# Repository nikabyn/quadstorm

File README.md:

# Project quadstorm (C010 Principles of Mobile Robotics)

## Architecture

## Mainboard

## Parts-List:
- [BT2.0 550mAh 1S Battery](https://betafpv.com/products/bt2-0-550mah-1s-battery-4pcs#:~:text=Weight:%2013.99g/pc,VS%20450mAh%20Battery)
- IMU [BMI323](https://www.bosch-sensortec.com/products/motion-sensors/imus/bmi323/)
- Motors: [4x 2S Bldc 1503](https://www.amazon.de/dp/B0CK2KT3R3)
- ESP32-C6 ([ESP32-C6 Supermini](https://wiki.raudys.com/doku.php?id=esp32:esp32-c6_super_mini_board) / [DFR1117](https://wiki.dfrobot.com/SKU_DFR1117_Beetle_ESP32_C6))
- 74LS04 (Hex-Inverter), 74LS138 3-to-8 demux)
- [FVT LittleBee ESC 20A 2-4S](https://de.aliexpress.com/item/1005010298051292.html)
- Generic DJI compatible props
- 3d Printed Frame
- Custom Mainboard (manufactured via CNC Router)
- 12 M2x8 Screws

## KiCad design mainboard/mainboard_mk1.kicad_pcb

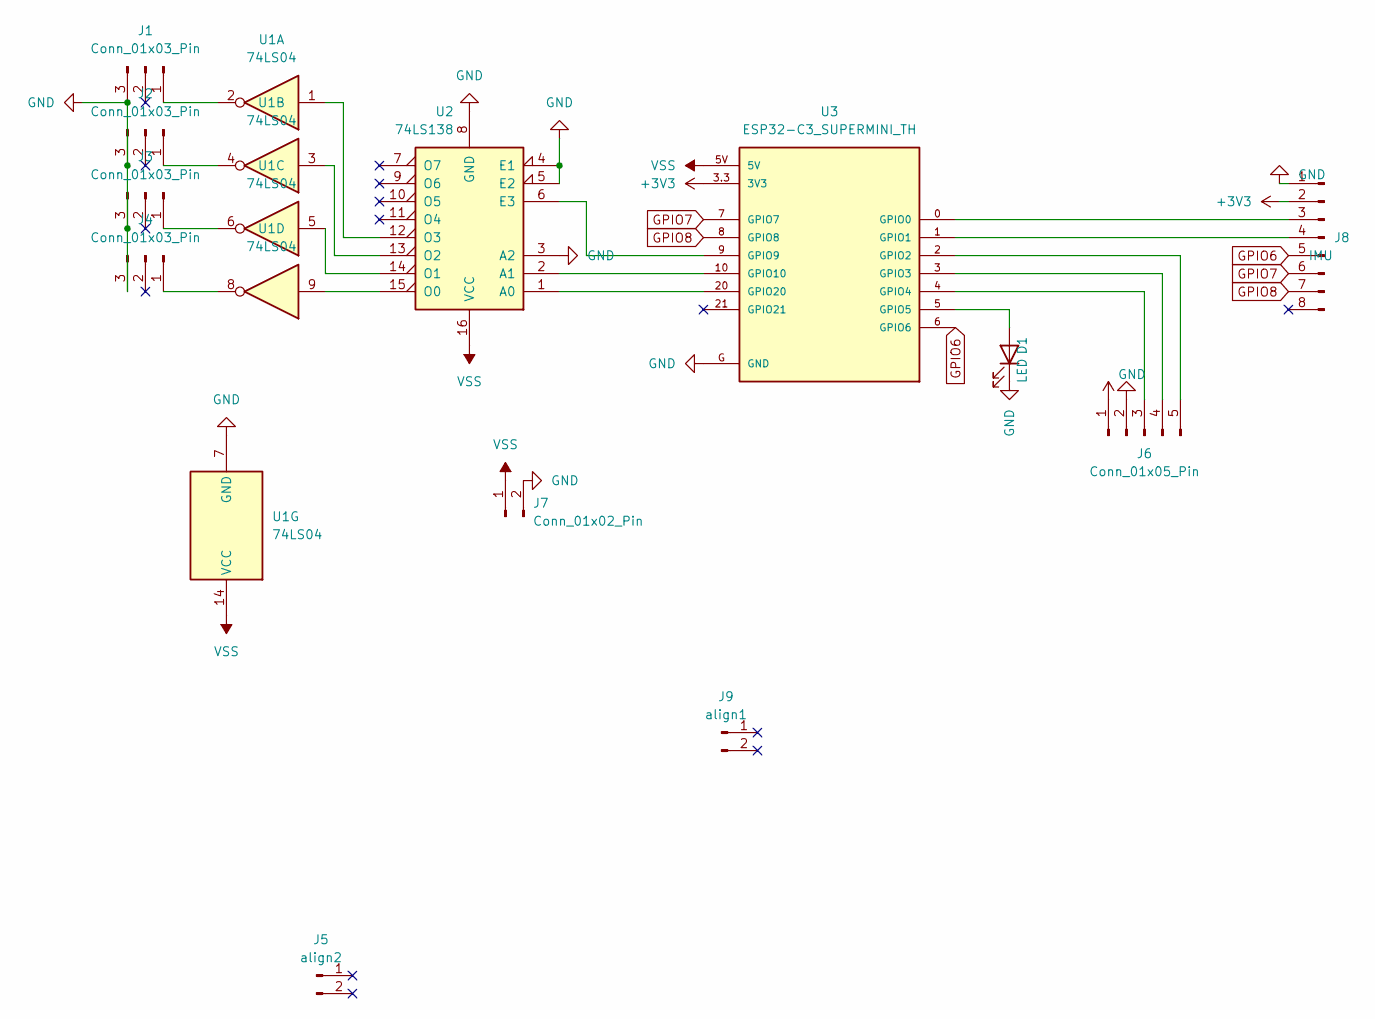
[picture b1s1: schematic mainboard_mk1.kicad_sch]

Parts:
D1: LED; LED_D3.0mm
J1, J2, J3, J4: Conn_01x03_Pin; PinHeader_1x03_P2.54mm_Vertical
J5: align2; PinHeader_1x02_P2.54mm_Vertical
J6: Conn_01x05_Pin; PinHeader_1x06_P2.54mm_Horizontal
J7: Conn_01x02_Pin; PinHeader_1x02_P2.54mm_Vertical
J8: IMU; PinHeader_1x08_P2.54mm_Vertical
J9: align1; PinHeader_1x02_P2.54mm_Vertical
U1: 74LS04; DIP-14_W7.62mm
U2: 74LS138; DIP-16_W7.62mm
U3: ESP32-C3_SUPERMINI_TH; MODULE_ESP32-C3_SUPERMINI_TH

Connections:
+3V3: J6.1, J8.2, U3.3.3 (3V3)
GND: D1.1 (K), J1.3, J2.3, J3.3, J4.3, J6.2, J7.2, J8.1, U1.7 (GND), U2.3 (A2), U2.4 (E1), U2.5 (E2), U2.8 (GND), U3.G (GND)
GPIO6: J8.5, U3.6 (GPIO6)
GPIO7: J8.6, U3.7 (GPIO7)
GPIO8: J8.7, U3.8 (GPIO8)
unnamed: D1.2 (A), U3.5 (GPIO5)
unnamed: J1.1, U1.2
unnamed: J2.1, U1.4
unnamed: J3.1, U1.6
unnamed: J4.1, U1.8
unnamed: J6.3, U3.4 (GPIO4)
unnamed: J6.4, U3.3 (GPIO3)
unnamed: J6.5, U3.2 (GPIO2)
unnamed: J8.3, U3.0 (GPIO0)
unnamed: J8.4, U3.1 (GPIO1)
unnamed: U2.1 (A0), U3.20 (GPIO20)
unnamed: U2.2 (A1), U3.10 (GPIO10)
unnamed: U2.6 (E3), U3.9 (GPIO9)
unnamed: U1.9, U2.15 (O0)
unnamed: U1.5, U2.14 (O1)
unnamed: U1.3, U2.13 (O2)
unnamed: U1.1, U2.12 (O3)
VSS: J7.1, U1.14 (VCC), U2.16 (VCC), U3.5V

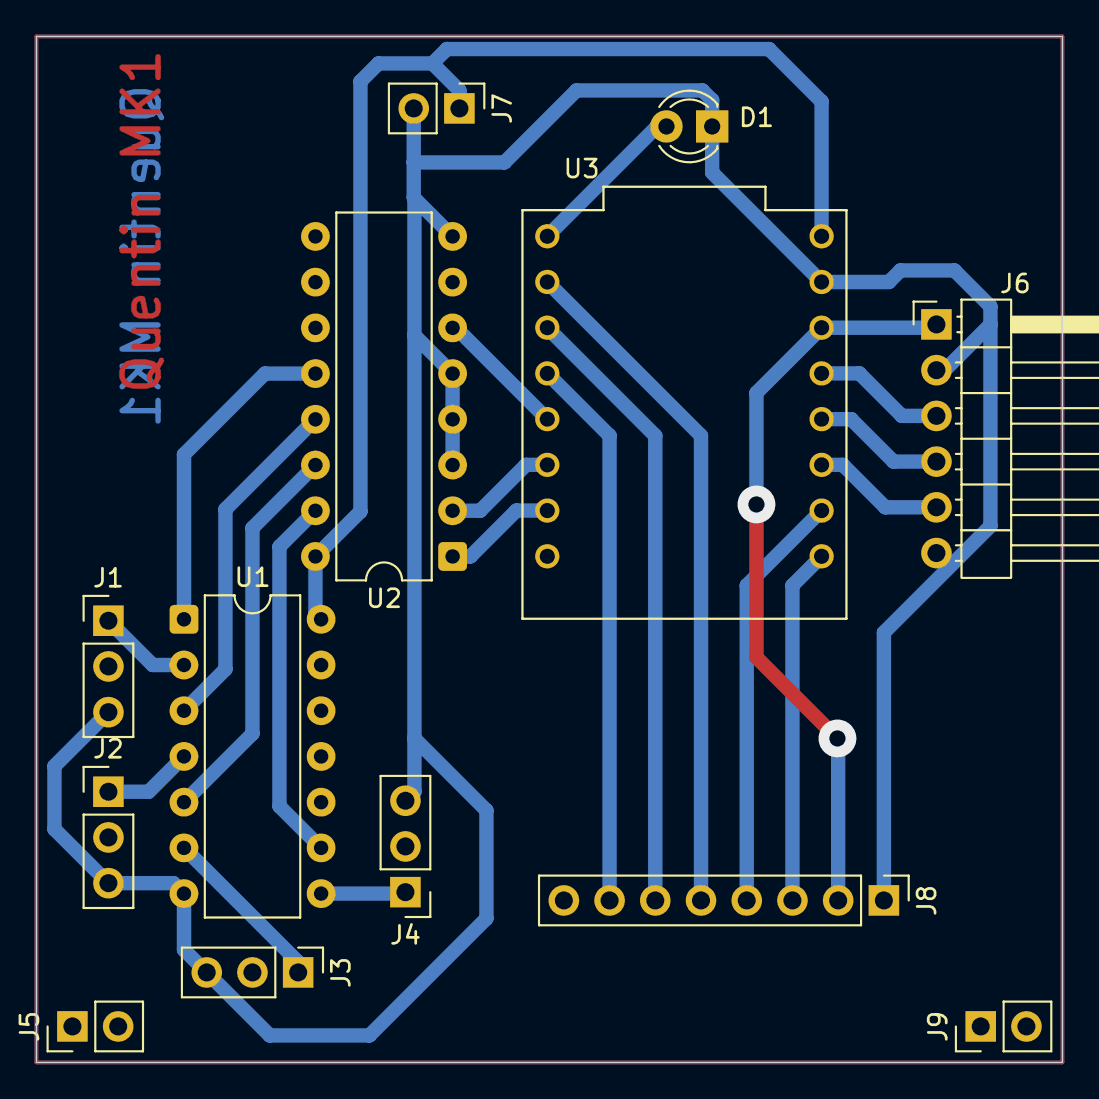
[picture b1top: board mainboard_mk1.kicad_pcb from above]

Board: 2 copper layers, 57.0 x 57.0 mm, 13 parts (0 on the bottom side), 23 nets.

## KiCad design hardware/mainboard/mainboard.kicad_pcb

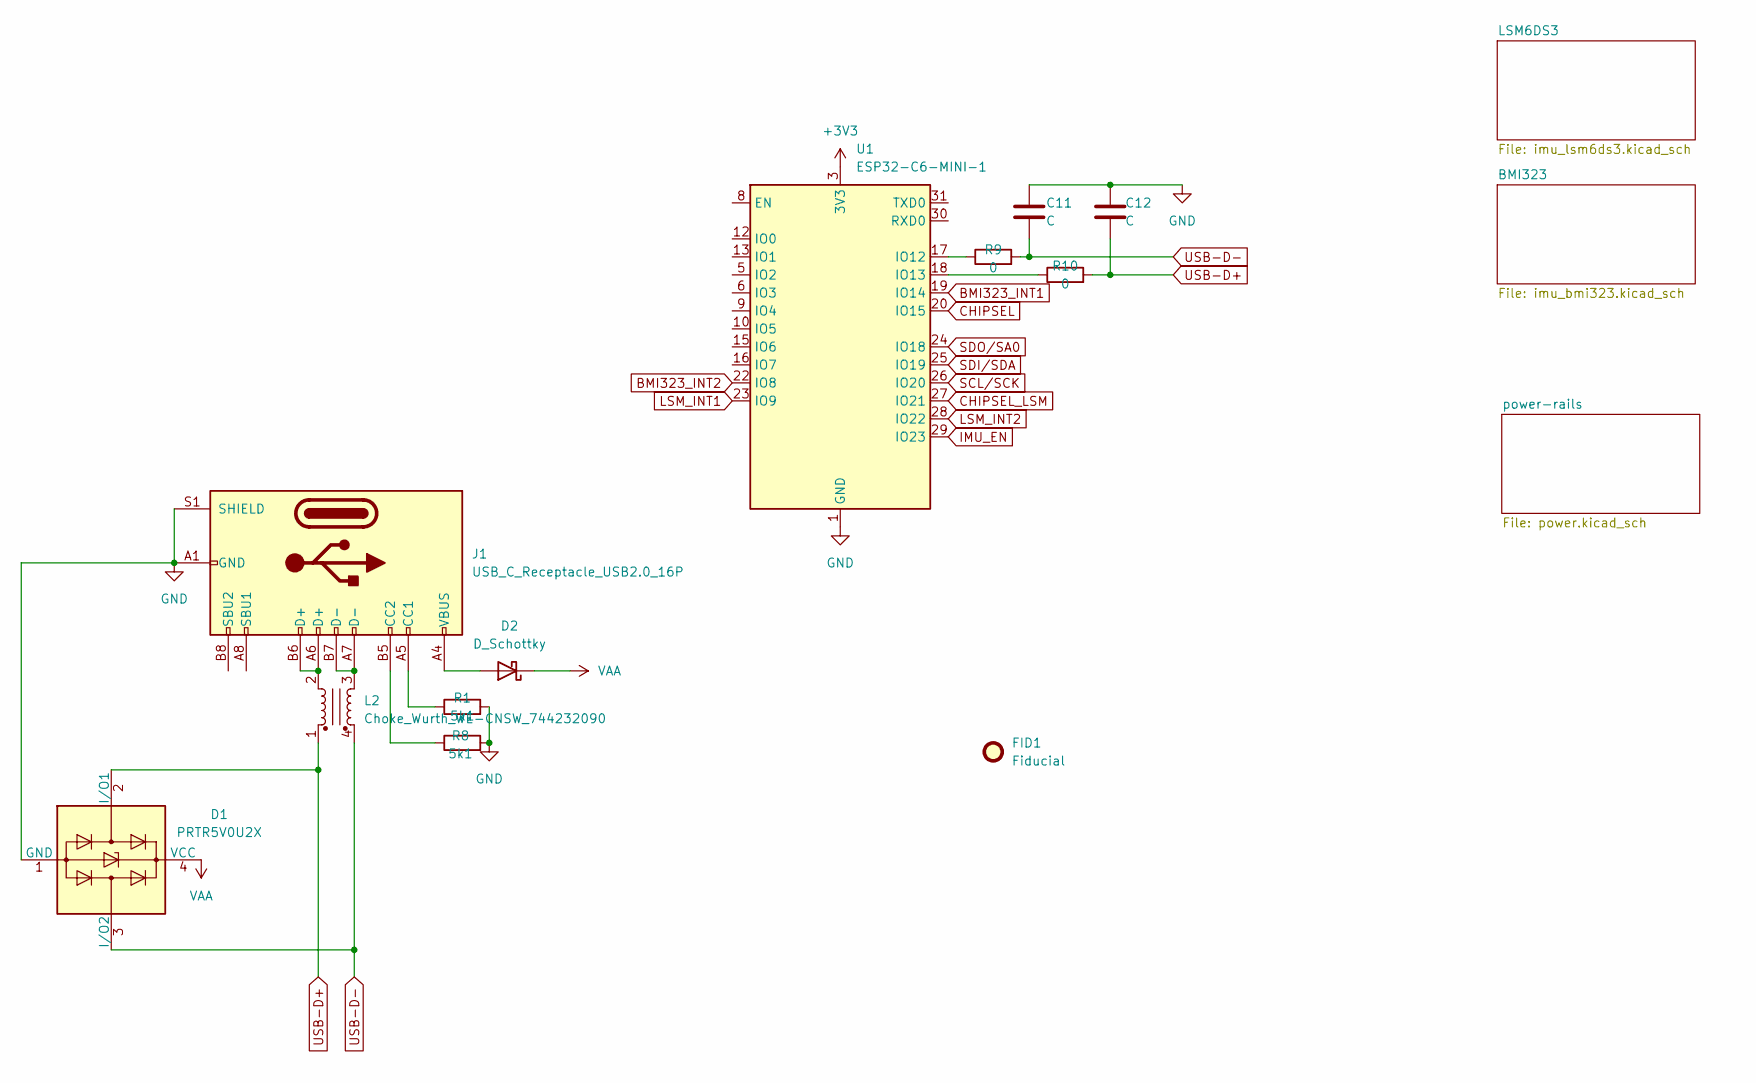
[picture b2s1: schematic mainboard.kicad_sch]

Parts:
C11, C12: C; C_0402_1005Metric
D1: PRTR5V0U2X; SOT-143
D2: D_Schottky; D_0805_2012Metric
FID1: Fiducial; Fiducial_0.5mm_Mask1.5mm
J1: USB_C_Receptacle_USB2.0_16P; USB_C_Receptacle_GCT_USB4105-xx-A_16P_TopMnt_Horizontal
L2: Choke_Wurth_WE-CNSW_744232090; L_CommonMode_Wurth_WE-CNSW-1206
R1, R8: 5k1; R_0603_1608Metric
R9, R10: 0; R_0603_1608Metric
U1: ESP32-C6-MINI-1

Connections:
+3V3: U1.3 (3V3); also elsewhere on the board
BMI323_INT1: U1.19 (IO14); also elsewhere on the board
BMI323_INT2: U1.22 (IO8); also elsewhere on the board
CHIPSEL: U1.20 (IO15); also elsewhere on the board
CHIPSEL_LSM: U1.27 (IO21); also elsewhere on the board
GND: C11.1, C12.1, D1.1 (GND), J1.A1 (GND), J1.A12 (GND), J1.B1 (GND), J1.B12 (GND), J1.S1 (SHIELD), R1.2, R8.2, U1.1 (GND), U1.2 (GND), U1.11 (GND), U1.14 (GND), U1.36 (GND), U1.37 (GND), U1.38 (GND), U1.39 (GND), U1.40 (GND), U1.41 (GND), U1.42 (GND), U1.43 (GND), U1.44 (GND), U1.45 (GND), U1.46 (GND), U1.47 (GND), U1.48 (GND), U1.49 (GND), U1.50 (GND), U1.51 (GND), U1.52 (GND), U1.53 (GND); also elsewhere on the board
IMU_EN: U1.29 (IO23); also elsewhere on the board
LSM_INT1: U1.23 (IO9); also elsewhere on the board
LSM_INT2: U1.28 (IO22); also elsewhere on the board
unnamed: D2.2 (A), J1.A4 (VBUS), J1.A9 (VBUS), J1.B4 (VBUS), J1.B9 (VBUS)
unnamed: J1.A5 (CC1), R1.1
unnamed: J1.B5 (CC2), R8.1
unnamed: J1.A6 (D+), J1.B6 (D+), L2.2
unnamed: J1.A7 (D-), J1.B7 (D-), L2.3
unnamed: R9.1, U1.17 (IO12)
unnamed: R10.1, U1.18 (IO13)
SCL/SCK: U1.26 (IO20); also elsewhere on the board
SDI/SDA: U1.25 (IO19); also elsewhere on the board
SDO/SA0: U1.24 (IO18); also elsewhere on the board
USB-D+: C12.2, D1.2 (I/O1), L2.1, R10.2
USB-D-: C11.2, D1.3 (I/O2), L2.4, R9.2
VAA: D1.4 (VCC), D2.1 (K); also elsewhere on the board

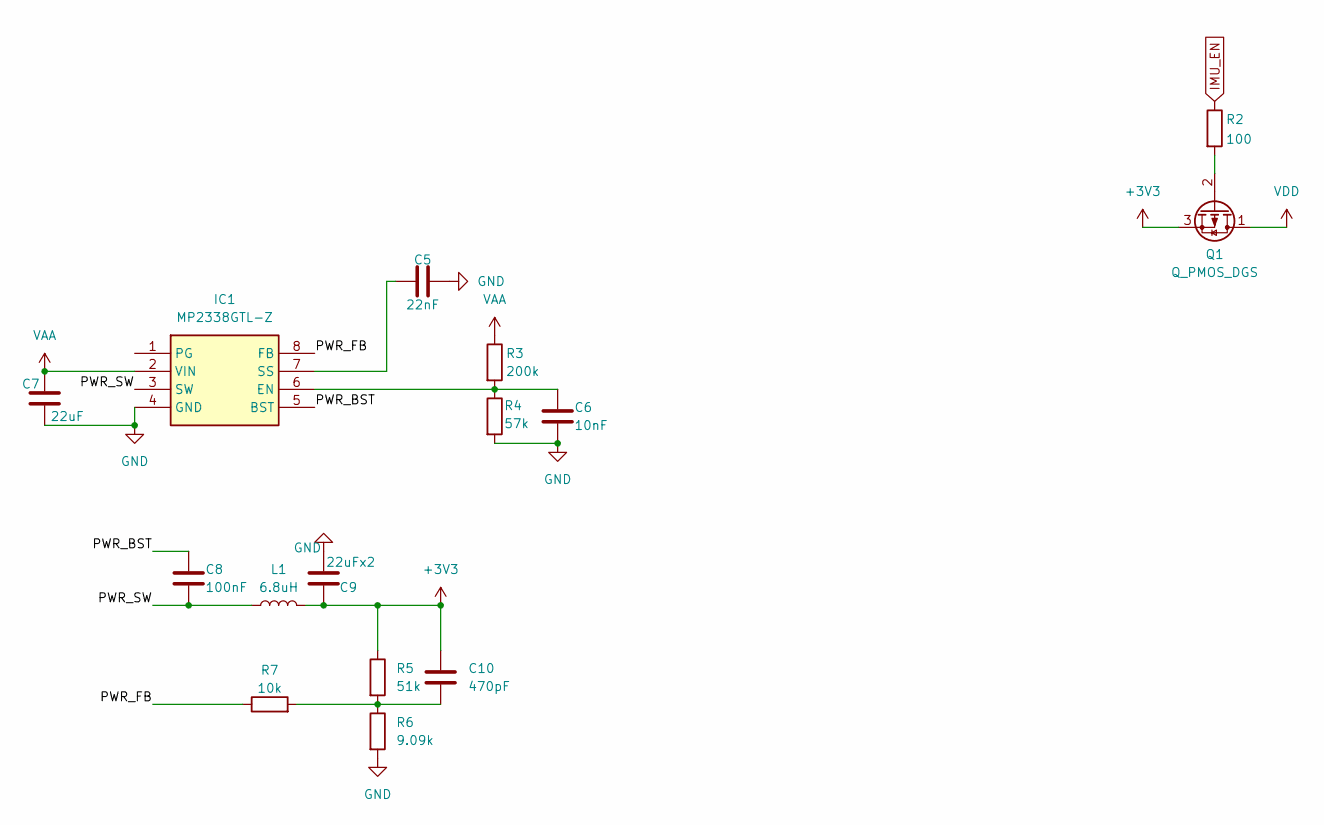
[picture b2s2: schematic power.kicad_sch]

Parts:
C5: 22nF; C_0402_1005Metric
C6: 10nF; C_0402_1005Metric
C7: 22uF; C_0402_1005Metric
C8: 100nF; C_0402_1005Metric
C9: 22uFx2; C_0402_1005Metric
C10: 470pF; C_0402_1005Metric
IC1: MP2338GTL-Z; MP2338GTLZ; Manufacturer_Part_Number MP2338GTL-Z; Mouser Part Number 946-MP2338GTL-Z
L1: 6.8uH; L_0805_2012Metric_Pad1.05x1.20mm_HandSolder
Q1: Q_PMOS_DGS; SOT-23-3
R2: 100; R_0603_1608Metric
R3: 200k; R_0603_1608Metric
R4: 57k; R_0603_1608Metric
R5: 51k; R_0603_1608Metric
R6: 9.09k; R_0603_1608Metric
R7: 10k; R_0603_1608Metric

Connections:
+3V3: C9.1, C10.1, L1.2, Q1.3 (S), R5.1; also elsewhere on the board
/power-rails/PWR_BST: C8.1, IC1.5 (BST)
/power-rails/PWR_FB: IC1.8 (FB), R7.1
/power-rails/PWR_SW: C8.2, IC1.3 (SW), L1.1
GND: C5.2, C6.2, C7.2, C9.2, IC1.4 (GND), R4.2, R6.2; also elsewhere on the board
IMU_EN: R2.1; also elsewhere on the board
unnamed: C10.2, R5.2, R6.1, R7.2
unnamed: C6.1, IC1.6 (EN), R3.2, R4.1
unnamed: C5.1, IC1.7 (SS)
unnamed: Q1.2 (G), R2.2
VAA: C7.1, IC1.2 (VIN), R3.1; also elsewhere on the board
VDD: Q1.1 (D); also elsewhere on the board

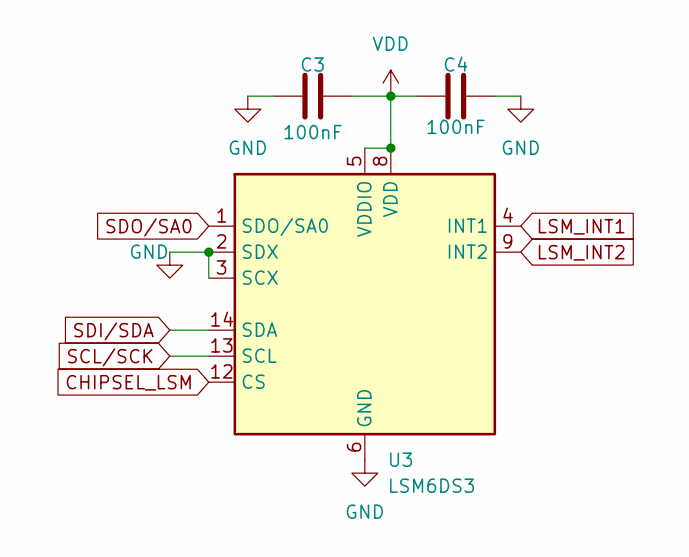
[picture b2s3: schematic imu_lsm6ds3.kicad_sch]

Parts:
C3, C4: 100nF; C_0402_1005Metric
U3: LSM6DS3; LGA-14_3x2.5mm_P0.5mm_LayoutBorder3x4y

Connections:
CHIPSEL_LSM: U3.12 (CS); also elsewhere on the board
GND: C3.1, C4.2, U3.2 (SDX), U3.3 (SCX), U3.6 (GND), U3.7 (GND); also elsewhere on the board
LSM_INT1: U3.4 (INT1); also elsewhere on the board
LSM_INT2: U3.9 (INT2); also elsewhere on the board
SCL/SCK: U3.13 (SCL); also elsewhere on the board
SDI/SDA: U3.14 (SDA); also elsewhere on the board
SDO/SA0: U3.1 (SDO/SA0); also elsewhere on the board
VDD: C3.2, C4.1, U3.5 (VDDIO), U3.8 (VDD); also elsewhere on the board

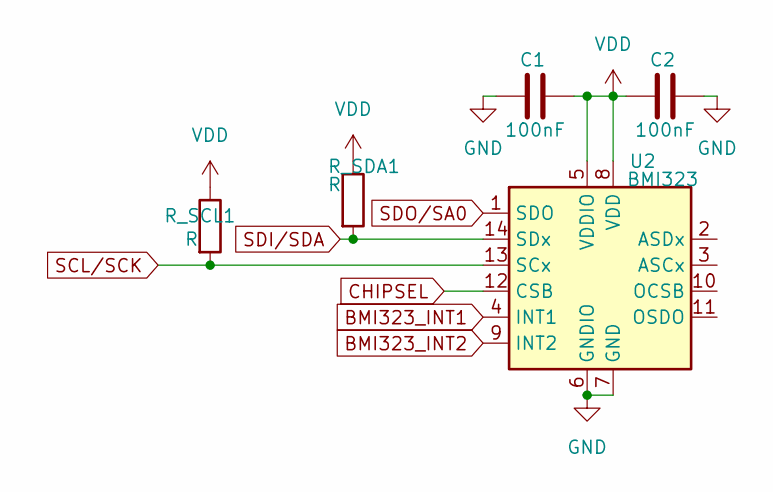
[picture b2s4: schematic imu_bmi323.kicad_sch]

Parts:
C1, C2: 100nF; C_0402_1005Metric
R_SCL1: R; R_0603_1608Metric
R_SDA1: R; R_0603_1608Metric
U2: BMI323; Bosch_LGA-14_3x2.5mm_P0.5mm

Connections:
BMI323_INT1: U2.4 (INT1); also elsewhere on the board
BMI323_INT2: U2.9 (INT2); also elsewhere on the board
CHIPSEL: U2.12 (CSB); also elsewhere on the board
GND: C1.1, C2.2, U2.6 (GNDIO), U2.7 (GND); also elsewhere on the board
SCL/SCK: R_SCL1.2, U2.13 (SCx); also elsewhere on the board
SDI/SDA: R_SDA1.2, U2.14 (SDx); also elsewhere on the board
SDO/SA0: U2.1 (SDO); also elsewhere on the board
VDD: C1.2, C2.1, R_SCL1.1, R_SDA1.1, U2.5 (VDDIO), U2.8 (VDD); also elsewhere on the board

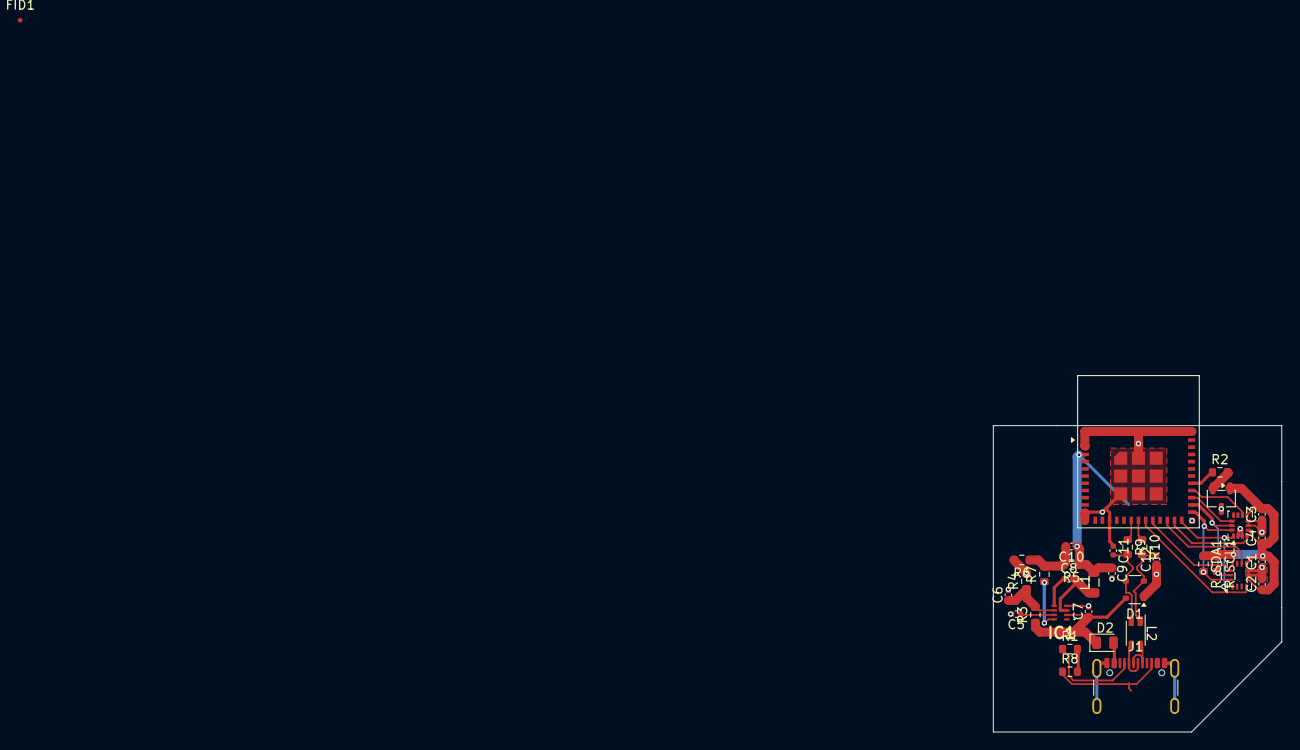
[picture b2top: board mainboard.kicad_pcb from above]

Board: 2 copper layers, 32.0 x 34.0 mm, 35 parts (0 on the bottom side), 30 nets.

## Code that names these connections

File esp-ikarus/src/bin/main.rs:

#![no_std]
#![no_main]
#![deny(
    clippy::mem_forget,
    reason = "mem::forget is generally not safe to do with esp_hal types, especially those \
    holding buffers for the duration of a data transfer."
)]

use embassy_time::{Duration, Instant, Timer};
use esp_backtrace as _;
use esp_hal::clock::CpuClock;
use esp_hal::timer::timg::TimerGroup;
use esp_hal::usb_serial_jtag::UsbSerialJtag;
use log::{info, warn};

// This creates a default app-descriptor required by the esp-idf bootloader.
// For more information see: <https://docs.espressif.com/projects/esp-idf/en/stable/esp32/api-reference/system/app_image_format.html#application-description>
esp_bootloader_esp_idf::esp_app_desc!();

// Initializes and arms the ESCs at GPIO5-GPIO8 and waits for input
// send a numeric ascii value 0..=1000 to change current throttle.
// send "RAMP" to enter a program to ramp the motor up and down.
// send "RAMP" again to leave.
//
// $ echo 100 > /dev/ttyACM0 # set throttle 100
// $ echo 1000 > /dev/ttyACM0 # set max throttle
// $ echo RAMP > /dev/ttyACM0 # enter ramping program

#[esp_rtos::main]
async fn main(_spawner: embassy_executor::Spawner) -> ! {
    esp_println::logger::init_logger_from_env();

    let config = esp_hal::Config::default().with_cpu_clock(CpuClock::max());
    let p = esp_hal::init(config);

    let timg0 = TimerGroup::new(p.TIMG0);
    let sw_interrupt = esp_hal::interrupt::software::SoftwareInterruptControl::new(p.SW_INTERRUPT);
    esp_rtos::start(timg0.timer0, sw_interrupt.software_interrupt0);

    info!("Embassy initialized!");

    let mut motors =
        // esp_ikarus::motors::rmt::Motors::dshot600(p.RMT, p.GPIO5, (p.GPIO6, p.GPIO7)).await;
    esp_ikarus::motors::rmt::Motors::oneshot125(p.RMT, p.GPIO19, (p.GPIO6, p.GPIO20)).await;
    // motors.arm_dshot().await;

    let (mut rx, _tx) = UsbSerialJtag::new(p.USB_DEVICE).into_async().split();
    let mut buf = [0; 5];
    let mut len = 0;
    let mut ramp = false;

    let mut throttle = 0;

    loop {
        len = rx.drain_rx_fifo(&mut buf[len..]);
        if len > 0 {
            throttle = match buf {
                [b'R', b'A', b'M', b'P', b'\n'] => {
                    ramp = !ramp;
                    continue;
                }
                [b'A', b'R', b'M', b'\n', ..] => {
                    ramp = false;
                    throttle = 0;
                    motors.arm_oneshot().await;
                    continue;
                }
                [a @ b'0'..=b'9', b'\n', ..] => (a - b'0') as u16,
                [b @ b'0'..=b'9', a @ b'0'..=b'9', b'\n', ..] => {
                    10 * (b - b'0') as u16 + (a - b'0') as u16
                }
                [c @ b'0'..=b'9', b @ b'0'..=b'9', a @ b'0'..=b'9', b'\n', ..] => {
                    100 * (c - b'0') as u16 + 10 * (b - b'0') as u16 + (a - b'0') as u16
                }
                [
                    d @ b'0'..=b'9',
                    c @ b'0'..=b'9',
                    b @ b'0'..=b'9',
                    a @ b'0'..=b'9',
                    b'\n',
                    ..,
                ] => {
                    1000 * (d - b'0') as u16
                        + 100 * (c - b'0') as u16
                        + 10 * (b - b'0') as u16
                        + (a - b'0') as u16
                }
                _ if len == 5 => {
                    warn!("discarding bytes");
                    len = 0;
                    continue;
                }
                _ if buf[0..len].contains(&b'\n') => {
                    warn!("discarding bytes");
                    len = 0;
                    continue;
                }
                _ => continue,
            }
            // .clamp(0, 2000);
            .clamp(0, 2047);
            log::info!("throttle: {throttle}");
        }

        if ramp {
            for throttle in 0..=2000 {
                let now = Instant::now();
                log::info!("throttle: {throttle}");
                motors.send_throttles([throttle; 4]).await;
                Timer::at(now.saturating_add(Duration::from_millis(2))).await;
            }
            throttle = 2000;

            let end = Instant::now().saturating_add(Duration::from_secs(3));
            while Instant::now() <= end {
                let now = Instant::now();
                motors.send_throttles([throttle; 4]).await;
                Timer::at(now.saturating_add(Duration::from_millis(2))).await;
            }

            for throttle in (0..=2000).rev() {
                motors.send_throttles([throttle; 4]).await;
                log::info!("throttle: {throttle}");
                Timer::after(Duration::from_millis(2)).await;
            }
            throttle = 0;

            let end = Instant::now().saturating_add(Duration::from_secs(1));
            while Instant::now() <= end {
                let now = Instant::now();
                motors.send_throttles([throttle; 4]).await;
                Timer::at(now.saturating_add(Duration::from_millis(2))).await;
            }
        }

        let now = Instant::now();
        motors.send_throttles([throttle; 4]).await;
        Timer::at(now.saturating_add(Duration::from_micros(2))).await;
    }
}

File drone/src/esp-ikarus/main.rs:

#![no_std]
#![no_main]
#![deny(
    clippy::mem_forget,
    reason = "mem::forget is generally not safe to do with esp_hal types, especially those \
    holding buffers for the duration of a data transfer."
)]

use core::mem::MaybeUninit;

use base64::Engine;
use embassy_executor::Spawner;
use embassy_sync::blocking_mutex::raw::NoopRawMutex;
use embassy_sync::lazy_lock::LazyLock;
use embassy_time::{Duration, Timer};
use esp_backtrace as _;
use esp_hal::clock::CpuClock;
use esp_hal::timer::timg::TimerGroup;
use esp_ikarus::bmi323;
use log::info;

// This creates a default app-descriptor required by the esp-idf bootloader.
// For more information see: <https://docs.espressif.com/projects/esp-idf/en/stable/esp32/api-reference/system/app_image_format.html#application-description>
esp_bootloader_esp_idf::esp_app_desc!();

#[esp_rtos::main]
async fn main(spawner: Spawner) -> ! {
    esp_println::logger::init_logger_from_env();

    let config = esp_hal::Config::default().with_cpu_clock(CpuClock::max());
    let p = esp_hal::init(config);

    let timg0 = TimerGroup::new(p.TIMG0);
    let sw_interrupt = esp_hal::interrupt::software::SoftwareInterruptControl::new(p.SW_INTERRUPT);
    esp_rtos::start(timg0.timer0, sw_interrupt.software_interrupt0);

    info!("Embassy initialized!");

    let poci = p.GPIO0;
    let imu_cs = p.GPIO1;
    let pico = p.GPIO2;
    let sck = p.GPIO3;
    let imu_int1 = p.GPIO14;
    let imu_spi = p.SPI2;
    let imu_dma = p.DMA_CH0;

    // SPI
    log::info!("IMU init..");

    let mut imu = bmi323::BMI323::new(imu_spi, sck, pico, poci, imu_dma, imu_cs, imu_int1);
    imu.configure().await.unwrap();

    log::info!("IMU ready");

    let (imu_rx, imu_task) = {
        static mut CHANNEL_BUF: MaybeUninit<[bmi323::Sample; 8]> = core::mem::MaybeUninit::uninit();
        static mut CHANNEL: LazyLock<
            embassy_sync::zerocopy_channel::Channel<'static, NoopRawMutex, bmi323::Sample>,
        > = LazyLock::new(|| {
            #[allow(static_mut_refs)]
            embassy_sync::zerocopy_channel::Channel::new(unsafe { CHANNEL_BUF.assume_init_mut() })
        });

        #[allow(static_mut_refs)]
        imu.start(unsafe { CHANNEL.get_mut() })
    };

    spawner.must_spawn(imu_consumer(imu_rx));
    spawner.must_spawn(imu_task);

    loop {
        log::info!("still alive");
        Timer::after(Duration::from_secs(10)).await;
    }
}

#[embassy_executor::task]
async fn imu_consumer(
    mut rx: embassy_sync::zerocopy_channel::Receiver<'static, NoopRawMutex, bmi323::Sample>,
) {
    loop {
        let sample = *rx.receive().await;
        rx.receive_done();

        let bmi323::Sample { gy, xl, time } = sample;

        let mut sample_bytes = [0; { (4 * 3 * 2) + 2 }];
        gy.into_iter()
            .flat_map(f32::to_le_bytes)
            .chain(xl.into_iter().flat_map(f32::to_le_bytes))
            .chain(time.to_le_bytes().into_iter())
            .zip(sample_bytes.iter_mut())
            .for_each(|(a, b)| *b = a);

        let mut base64_bytes = [0; 64];
        let len = base64::prelude::BASE64_STANDARD_NO_PAD
            .encode_slice(sample_bytes, &mut base64_bytes)
            .unwrap();
        let b64_str = str::from_utf8(&base64_bytes[0..len]).unwrap();

        info!("{sample:0.5?}, B64:{b64_str}");
    }
}

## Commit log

2025-10-17 Add README.
2025-11-03 added potential parts list
2025-11-03 hello world setup
2025-11-04 very basic imu test setup
2025-11-07 add initial crates for remote controller
2025-11-16 mainboard rev0
2025-11-16 rev1
2025-11-16 mainboard rev1
2025-11-16 mainboard edits
2025-11-18 feat(imu): gather IMU readings via SPI
2025-11-24 feat(imu): raw data visualization
2025-12-01 info docs
2025-12-04 feat(imu): implement bmi323
2025-12-05 feat(esc): implement basic motor driver using servo pwm
2025-12-05 doc(esc): add BLHeli_S manual
2025-12-18 feat(motors): implement OneShot125/42
    WIP might not work
2025-12-18 one frame arm
2025-12-18 feat(motors): implement DShot300
2025-12-19 simple frame
2025-12-19 feat(motors): use AsRef for Protocol
2025-12-19 feat(motors): implement dshot 150/300/600
2026-01-04 feat(motors): transform motor signal range
2026-01-14 feat(esp_now): remove 'static in some places
2026-01-14 feat(esp_now): remove ’static in even more places
2026-01-14 feat(esp_now): Implement initial communication
2026-01-16 feat(esp_now): split imports
2026-01-16 feat(merge_everything): merge folders
2026-01-16 feat(merge_everything): fix all build errors for drone
2026-01-16 feat(merge_evergything): move all esp code into single workspace
2026-01-16 feat(esp_now): integrate into drone crate
2026-01-23 feat(merge_everything): integrate imu
2026-01-23 feat(merge_everything): clean up and fix lints
2026-01-23 feat(merge_everything): clean up main functions
2026-02-06 change io pins for mainboard
2026-02-10 feat(logging): use probe-rs
2026-02-11 feat(remote): add initial terminal remote control interface
2026-02-12 modify pins for mainboard
2026-02-12 feat(workspace): add global workspace
2026-02-12 feat(remote): decode defmt in separate thread
2026-02-12 feat(android): add initial android app
2026-02-17 add current mainboard mk1 rev
2026-02-17 mk1 3d view done
2026-02-18 add setup
2026-02-18 feat(messages): add mpsc channel
2026-02-18 feat(message): en/decode message frames
2026-02-19 feat(message): initial message send
2026-02-19 feat(message): logs tab for remote
2026-02-19 feat(message): fully working remote<->drone messages
2026-02-19 feat(message): add custom defmt logger for drone
2026-02-19 feat(message): print logs from drone
2026-02-20 feat(sensor_fusion): implement complementary filter and pid controller for roll, pitch and yaw
2026-02-20 feat(sensor_fusion): fix filter
2026-02-20 feat(sensor_fusion): control loops are now controlling
2026-02-20 feat(sensor_fusion): fix motor mapping
2026-02-20 fix(sensor_fusion):    
2026-02-21 feat(message): add remote terminal repl for messages
2026-02-21 feat(message): add readme to remote-terminal
2026-02-24 fix(arm_confirm): refactor drone control loop
2026-02-24 feat(arm_confirm): send arm confirm continually from terminal
2026-02-24 fix(arm_confirm): properly receive inputs
2026-02-24 fix(imu_shenanigans): fix rust analyzer
2026-02-24 fix(imu_shenanigans): fix spi transactions
2026-02-25 feat(ui): add feature from main
2026-02-25 fix(pid_targets): set yaw as rotation speed target
2026-02-25 fix(motors): set lower motor bound when armed
2026-02-25 feat(gamepad): add arming buttons mapping
2026-02-25 feat(metrics_gui): add bevy_egui and egui_plot
2026-02-25 feat(gui): new overall layout
2026-02-25 feat(gui): finish layout
2026-02-26 feat(gui): send pings every 500ms, add reset button
2026-02-26 feat(gui): display logs
2026-02-26 fix(gui): fix drone logs
2026-02-26 fix(gui): set keep_armed in settings
2026-02-26 chore: rename crates
2026-02-26 feat(gui): track gamepad status
2026-02-26 fix(pid): prevent integrator windup
2026-02-26 fix(mototrs): wrap rmt transmit and multiplex switching in critical section
2026-02-26 feat(whatever): fix mapping
2026-02-26 feat(whatever): add tuning ui for kp, ki, kd
2026-02-26 readme progress
